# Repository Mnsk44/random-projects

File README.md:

# random-projects

### Some random projects for personal use / proof of concept etc.

 - Automated window blinds (arduino)
 - Railway scheduler (Java/Android)

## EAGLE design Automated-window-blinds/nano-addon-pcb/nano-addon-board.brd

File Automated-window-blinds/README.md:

# Window blind automation DIY project

### Current status: proof-of-concept (waiting to be continued)

Arduino Nano and ESP8266 based multiple window automation system.
Webserver-code is for the "master"-nano, that will distribute the requests to
respective nanos (or this functionality will be centralized to some other 
home-server eg. RPi)

Includes currently:
 - Basic Webserver code used in the proof of concept testing
 - Some kind of PCB-board layout that supports LDR, Potentiometer input and servo output + ESP8266-plugin
 - 3D-printable adapter between servo and D-shaft

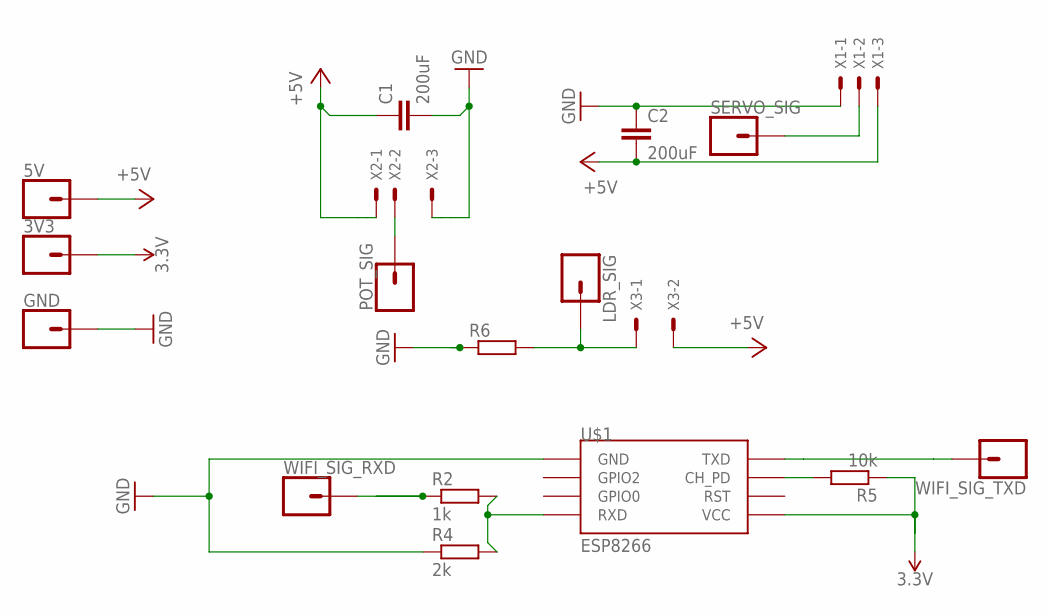
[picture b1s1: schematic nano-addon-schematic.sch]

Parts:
3V3, 5V: CONN_01; 1X01
C1, C2: 200uF; C050-030X075
GND: CONN_01; 1X01
LDR_SIG: CONN_01; 1X01
POT_SIG: CONN_01; 1X01
R2: 1k; 0204/7
R4: 2k; 0204/7
R5: 10k; 0204/7
R6: R0204/7; 0204/7
SERVO_SIG: CONN_01; 1X01
U$1: ESP8266; ESP01
WIFI_SIG_RXD: CONN_01; 1X01
WIFI_SIG_TXD: CONN_01; 1X01
X1, X2: KK-156-3
X3: KK-156-2

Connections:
3.3V: 3V3.1, R5.1, U$1.VCC
+5V: 5V.1, C1.1, C2.2, X1.3, X2.1, X3.2
GND: C1.2, C2.1, GND.1, R4.1, R6.1, U$1.GND, X1.1, X2.3
LDR_SIG: LDR_SIG.1, R6.2, X3.1
unnamed: POT_SIG.1, X2.2
unnamed: R5.2, U$1.CH_PD
unnamed: R2.2, R4.2, U$1.RX (RXD)
SERVO_SIG: SERVO_SIG.1, X1.2
WIFI_SIG_RXD: R2.1, WIFI_SIG_RXD.1
WIFI_SIG_TXD: U$1.TX (TXD), WIFI_SIG_TXD.1

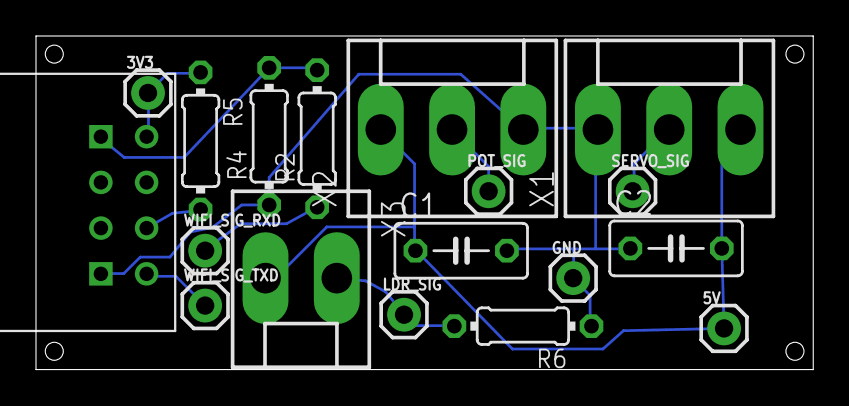
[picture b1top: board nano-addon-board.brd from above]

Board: 2 copper layers, 43.2 x 18.5 mm, 18 parts (0 on the bottom side), 10 nets.

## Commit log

2018-11-27 Moved to subfolder
2018-11-27 Added AWB-project
2018-11-27 Rename README.md.txt to README.md

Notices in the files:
parts and their libraries:
SparkFun-Connectors: Licensing: Creative Commons ShareAlike 4.0 International - https://creativecommons.org/licenses/by-sa/4.0
